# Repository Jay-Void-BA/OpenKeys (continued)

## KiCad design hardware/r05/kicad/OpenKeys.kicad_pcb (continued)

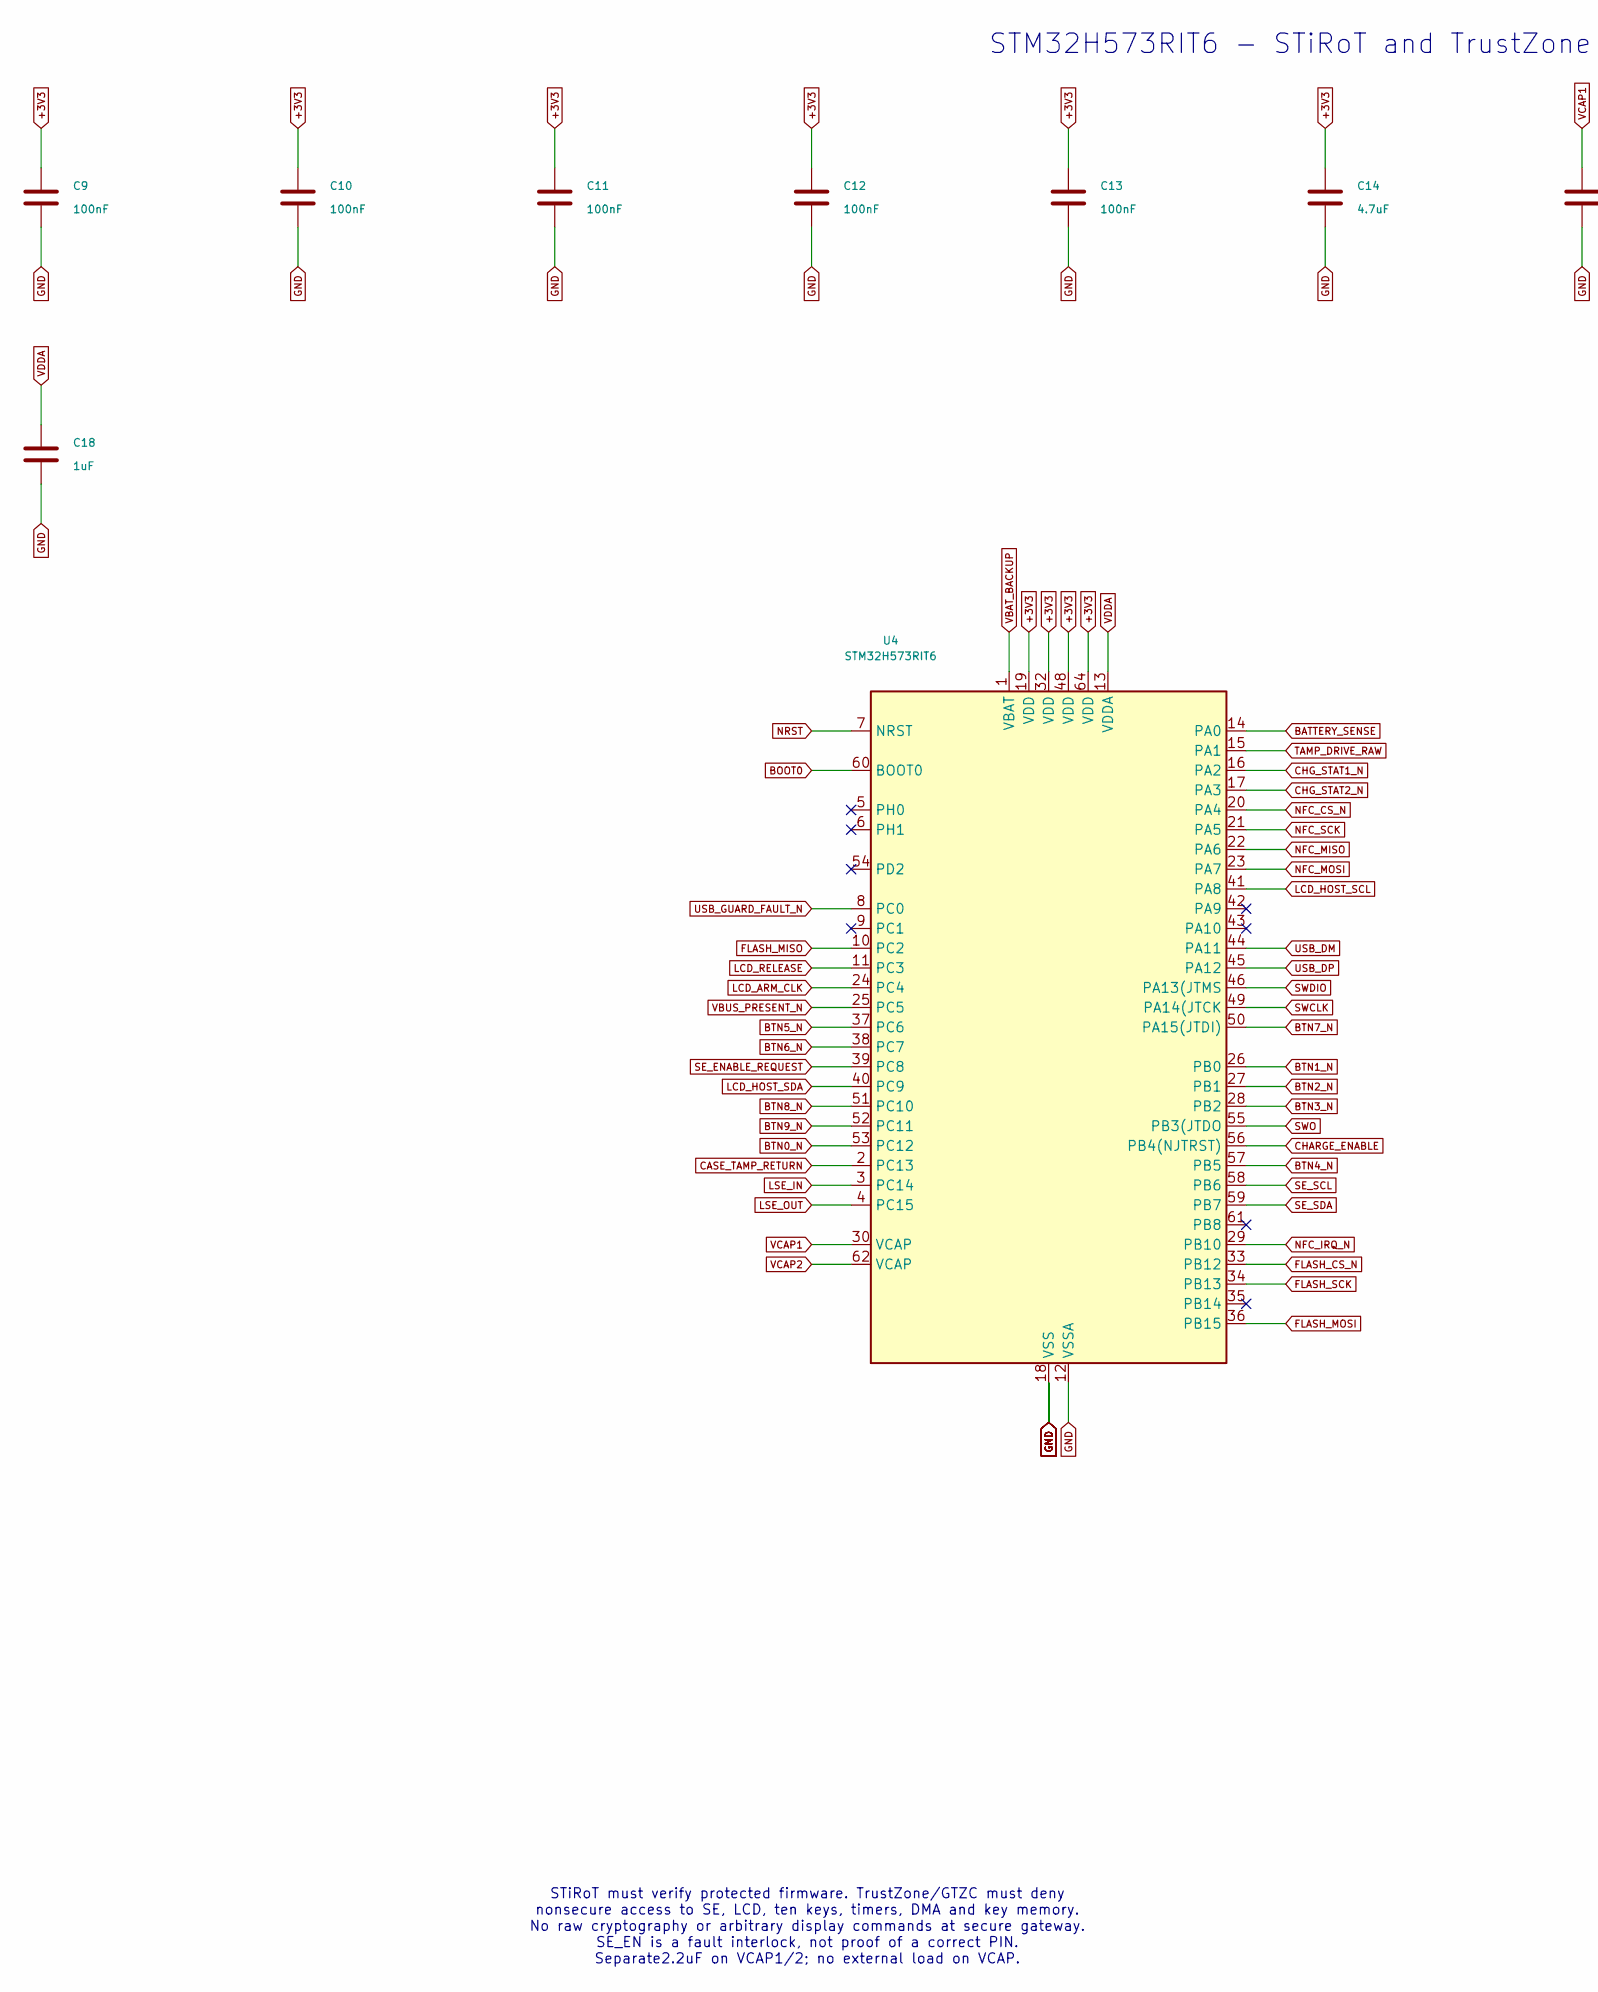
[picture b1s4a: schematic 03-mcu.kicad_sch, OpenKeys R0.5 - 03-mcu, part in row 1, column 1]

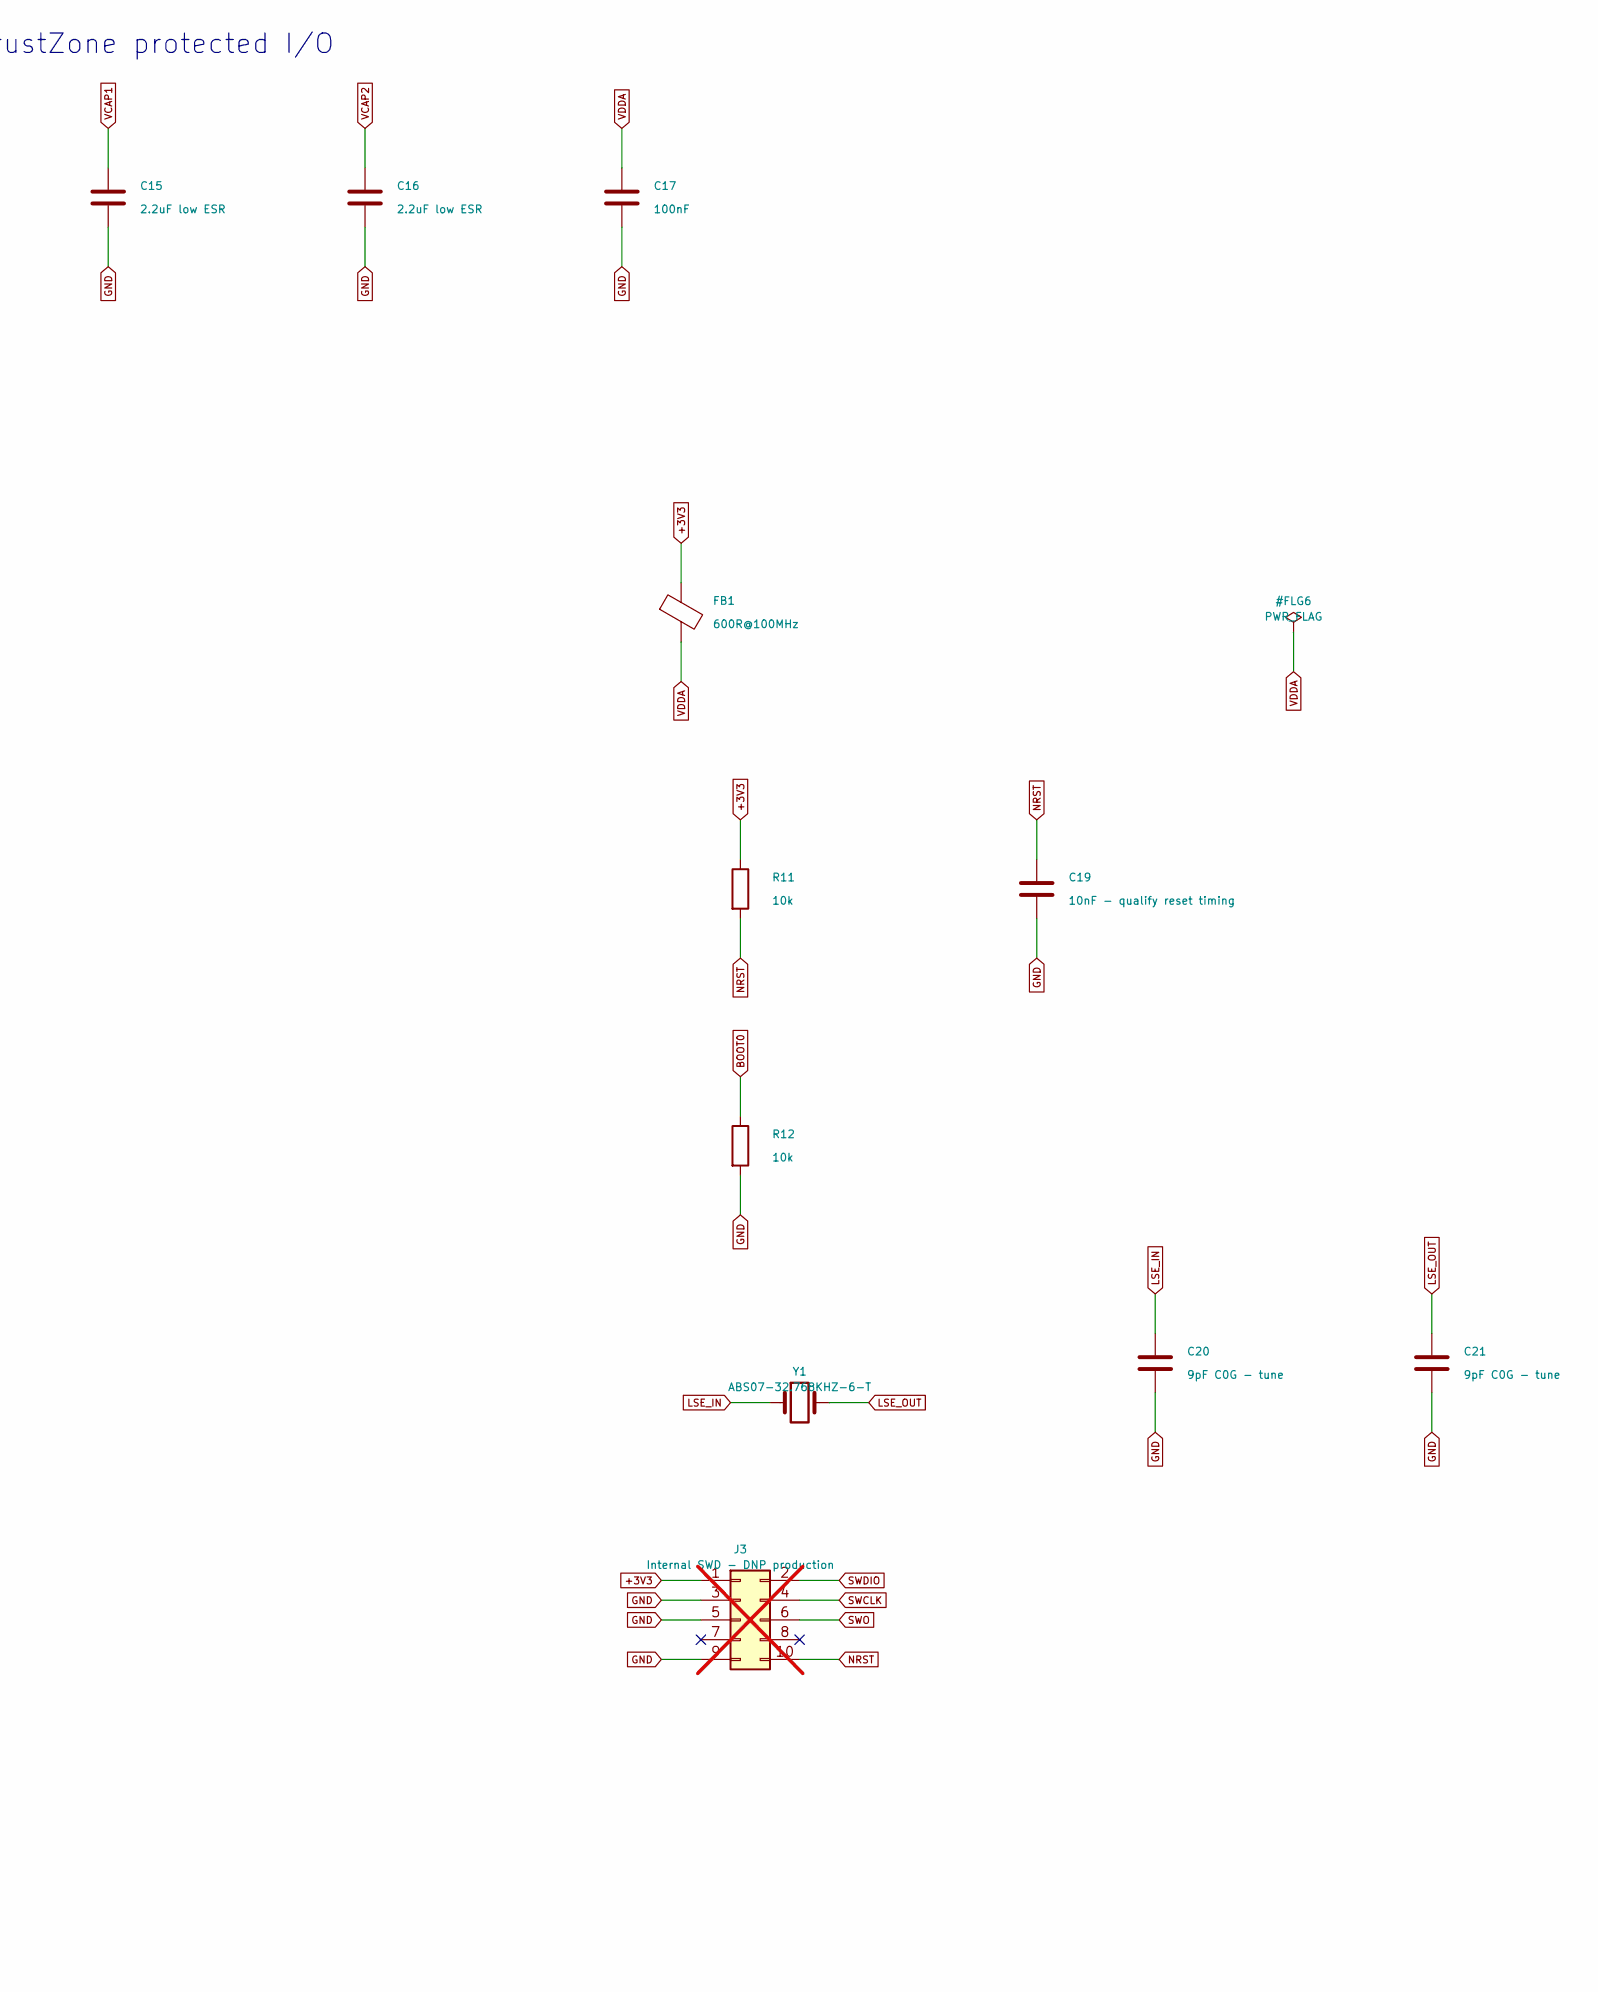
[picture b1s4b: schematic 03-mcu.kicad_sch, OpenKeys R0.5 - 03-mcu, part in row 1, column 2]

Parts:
C9, C10, C11, C12, C13, C17: 100nF; C_0603_1608Metric
C14: 4.7uF; C_0805_2012Metric
C15, C16: 2.2uF low ESR; C_0805_2012Metric
C18: 1uF; C_0805_2012Metric
C19: 10nF - qualify reset timing; C_0603_1608Metric
C20, C21: 9pF C0G - tune; C_0603_1608Metric
FB1: 600R@100MHz; L_0603_1608Metric
J3: Internal SWD - DNP production; PinHeader_2x05_P1.27mm_Vertical; not fitted
R11, R12: 10k; R_0603_1608Metric
U4: STM32H573RIT6; LQFP-64_10x10mm_P0.5mm
Y1: ABS07-32.768KHZ-6-T; Crystal_SMD_3215-2Pin_3.2x1.5mm

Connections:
+3V3: C9.1, C10.1, C11.1, C12.1, C13.1, C14.1, FB1.1, J3.1, R11.1, U4.19 (VDD), U4.32 (VDD), U4.48 (VDD), U4.64 (VDD); also elsewhere on the board
BATTERY_SENSE: U4.14 (PA0); also elsewhere on the board
BOOT0: R12.1, U4.60 (BOOT0)
BTN0_N: U4.53 (PC12); also elsewhere on the board
BTN1_N: U4.26 (PB0); also elsewhere on the board
BTN2_N: U4.27 (PB1); also elsewhere on the board
BTN3_N: U4.28 (PB2); also elsewhere on the board
BTN4_N: U4.57 (PB5); also elsewhere on the board
BTN5_N: U4.37 (PC6); also elsewhere on the board
BTN6_N: U4.38 (PC7); also elsewhere on the board
BTN7_N: U4.50 (PA15(JTDI)); also elsewhere on the board
BTN8_N: U4.51 (PC10); also elsewhere on the board
BTN9_N: U4.52 (PC11); also elsewhere on the board
CASE_TAMP_RETURN: U4.2 (PC13); also elsewhere on the board
CHARGE_ENABLE: U4.56 (PB4(NJTRST)); also elsewhere on the board
CHG_STAT1_N: U4.16 (PA2); also elsewhere on the board
CHG_STAT2_N: U4.17 (PA3); also elsewhere on the board
FLASH_CS_N: U4.33 (PB12); also elsewhere on the board
FLASH_MISO: U4.10 (PC2); also elsewhere on the board
FLASH_MOSI: U4.36 (PB15); also elsewhere on the board
FLASH_SCK: U4.34 (PB13); also elsewhere on the board
GND: C9.2, C10.2, C11.2, C12.2, C13.2, C14.2, C15.2, C16.2, C17.2, C18.2, C19.2, C20.2, C21.2, J3.3, J3.5, J3.9, R12.2, U4.12 (VSSA), U4.18 (VSS), U4.31 (VSS), U4.47 (VSS), U4.63 (VSS); also elsewhere on the board
LCD_ARM_CLK: U4.24 (PC4); also elsewhere on the board
LCD_HOST_SCL: U4.41 (PA8); also elsewhere on the board
LCD_HOST_SDA: U4.40 (PC9); also elsewhere on the board
LCD_RELEASE: U4.11 (PC3); also elsewhere on the board
LSE_IN: C20.1, U4.3 (PC14), Y1.1
LSE_OUT: C21.1, U4.4 (PC15), Y1.2
NFC_CS_N: U4.20 (PA4); also elsewhere on the board
NFC_IRQ_N: U4.29 (PB10); also elsewhere on the board
NFC_MISO: U4.22 (PA6); also elsewhere on the board
NFC_MOSI: U4.23 (PA7); also elsewhere on the board
NFC_SCK: U4.21 (PA5); also elsewhere on the board
NRST: C19.1, J3.10, R11.2, U4.7 (NRST); also elsewhere on the board
SE_ENABLE_REQUEST: U4.39 (PC8); also elsewhere on the board
SE_SCL: U4.58 (PB6); also elsewhere on the board
SE_SDA: U4.59 (PB7); also elsewhere on the board
SWCLK: J3.4, U4.49 (PA14(JTCK)
SWDIO: J3.2, U4.46 (PA13(JTMS)
SWO: J3.6, U4.55 (PB3(JTDO)
TAMP_DRIVE_RAW: U4.15 (PA1); also elsewhere on the board
USB_DM: U4.44 (PA11); also elsewhere on the board
USB_DP: U4.45 (PA12); also elsewhere on the board
USB_GUARD_FAULT_N: U4.8 (PC0); also elsewhere on the board
VBAT_BACKUP: U4.1 (VBAT); also elsewhere on the board
VBUS_PRESENT_N: U4.25 (PC5); also elsewhere on the board
VCAP1: C15.1, U4.30 (VCAP)
VCAP2: C16.1, U4.62 (VCAP)
VDDA: C17.1, C18.1, FB1.2, U4.13 (VDDA)

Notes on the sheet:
STM32H573RIT6 - STiRoT and TrustZone protected I/O
STiRoT must verify protected firmware. TrustZone/GTZC must deny nonsecure access to SE, LCD, ten keys, timers, DMA and key memory. No raw cryptography or arbitrary display commands at secure gateway. SE_EN is a fault interlock, not proof of a correct PIN. Separate2.2uF on VCAP1/2; no external load 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

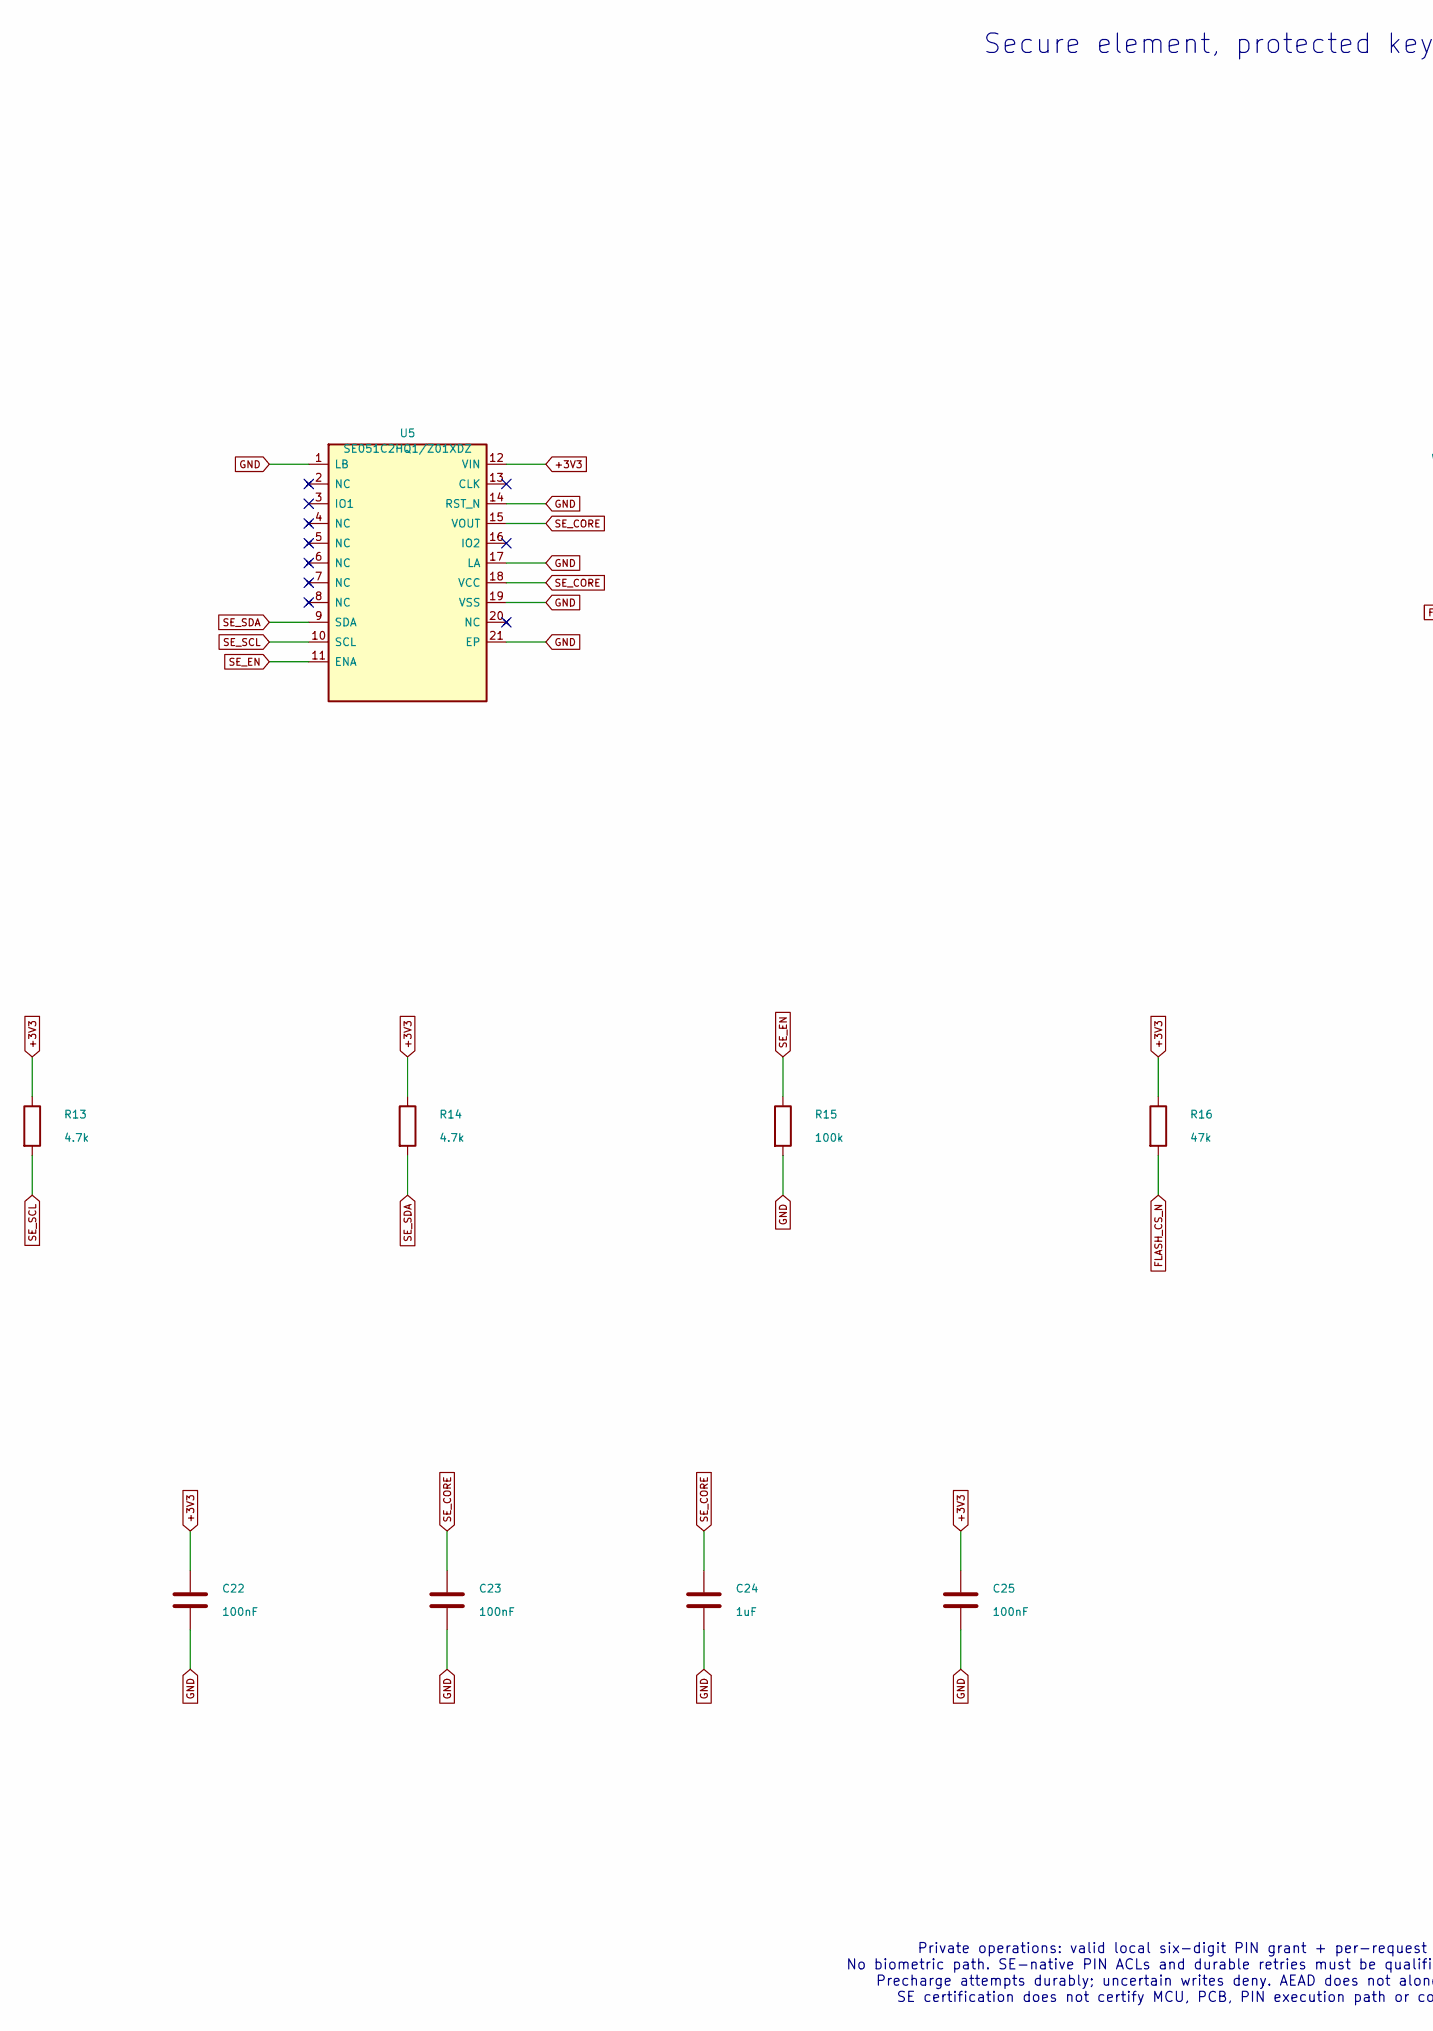
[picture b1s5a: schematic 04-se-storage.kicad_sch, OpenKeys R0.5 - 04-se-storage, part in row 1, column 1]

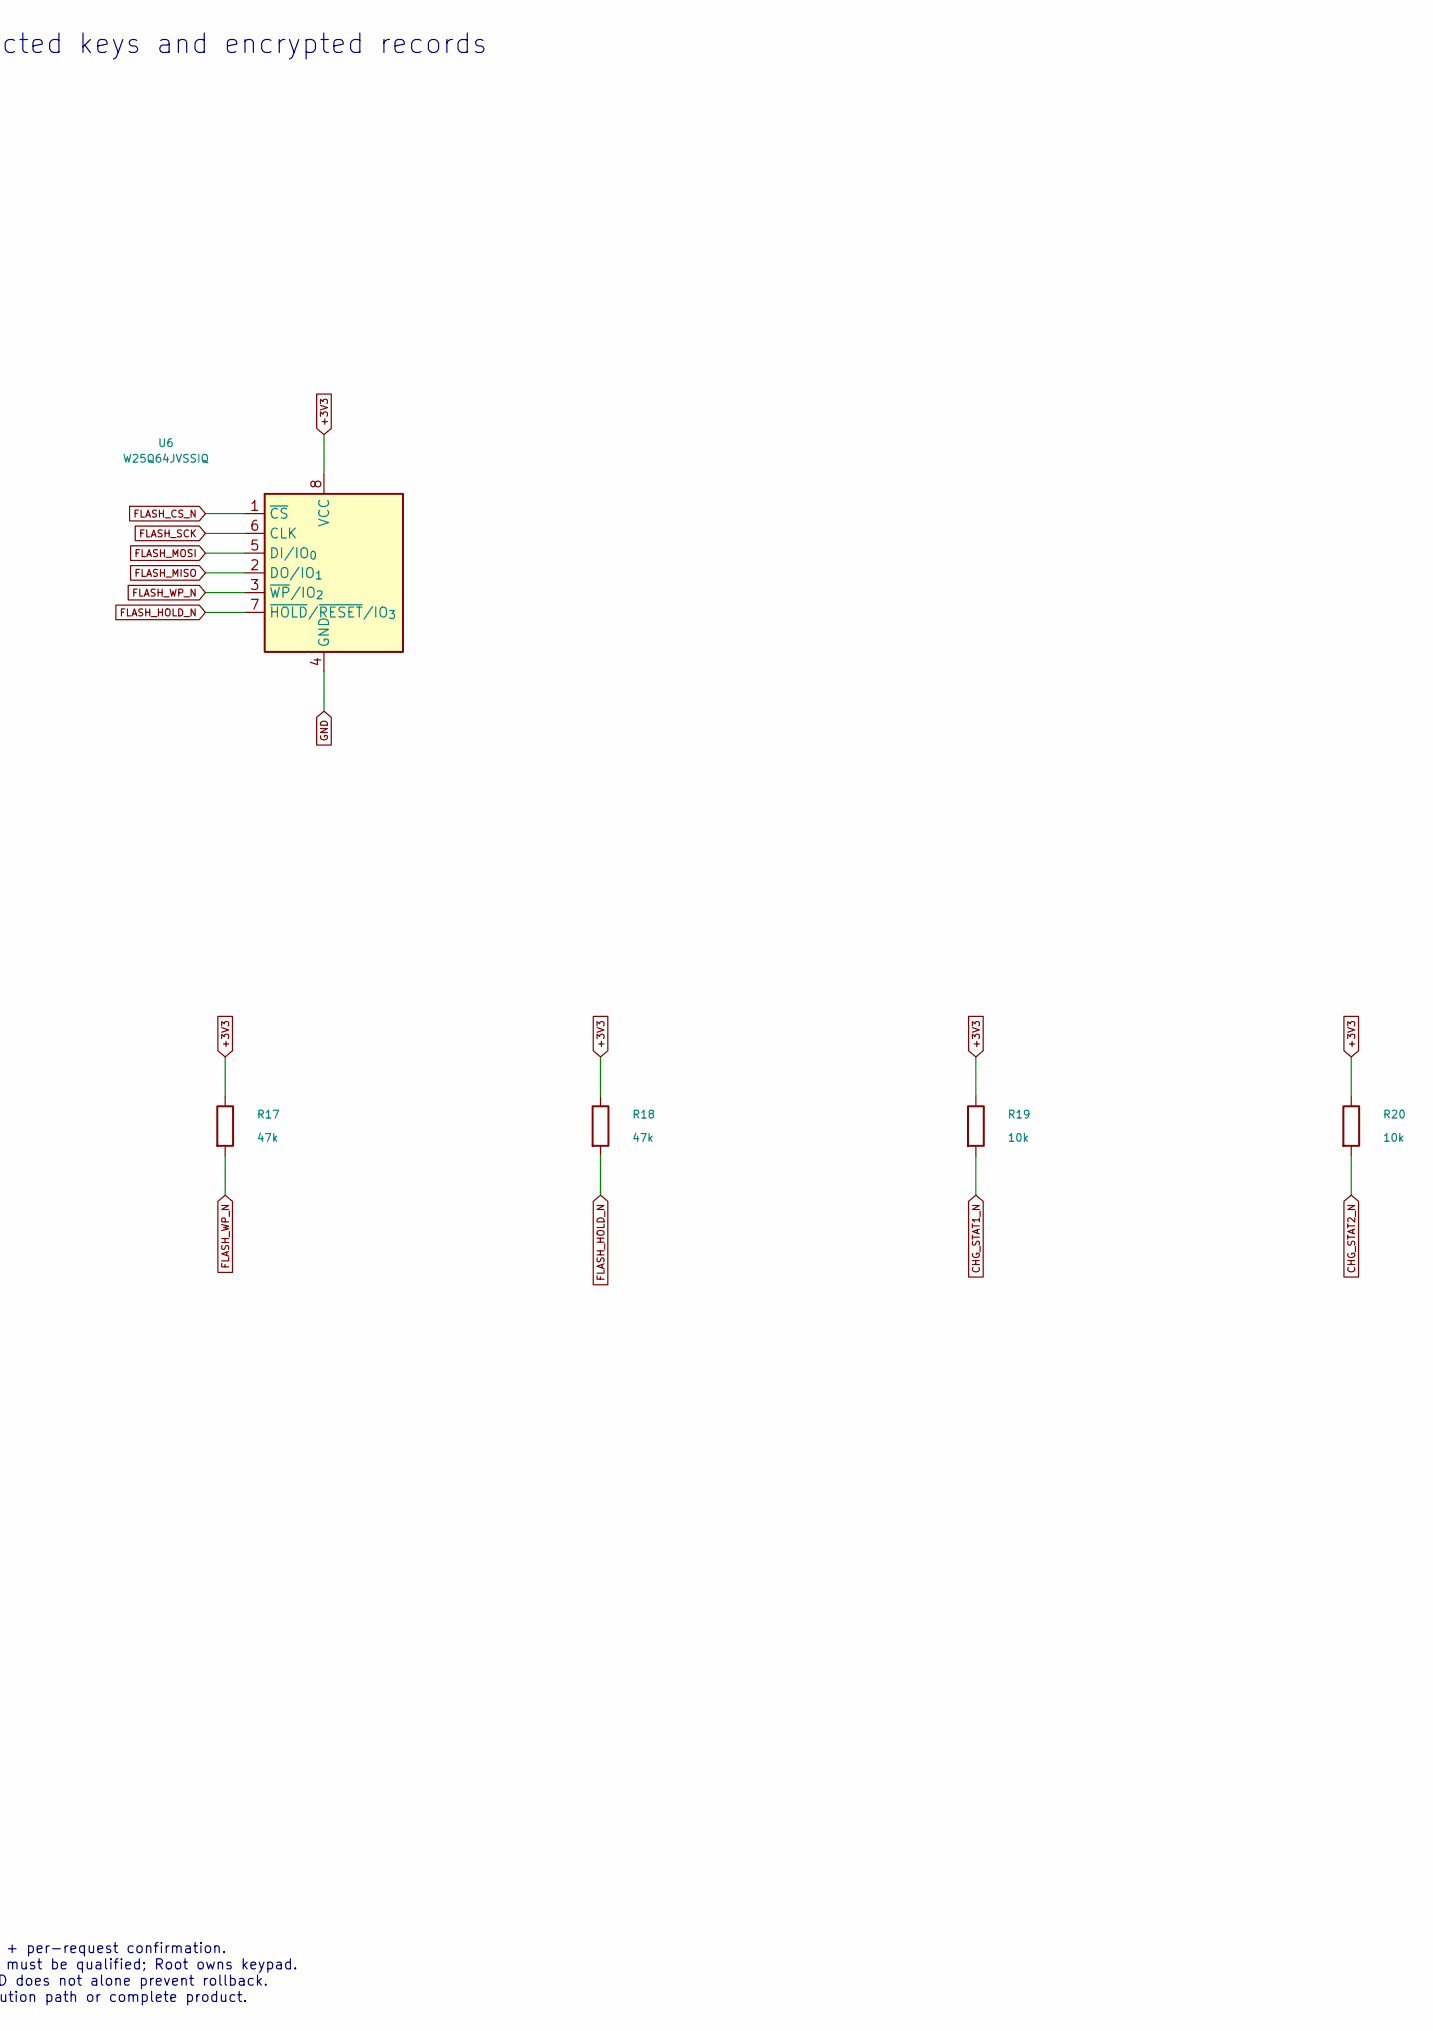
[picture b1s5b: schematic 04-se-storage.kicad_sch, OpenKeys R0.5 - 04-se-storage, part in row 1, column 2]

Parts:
C22, C23, C25: 100nF; C_0603_1608Metric
C24: 1uF; C_0805_2012Metric
R13, R14: 4.7k; R_0603_1608Metric
R15: 100k; R_0603_1608Metric
R16, R17, R18: 47k; R_0603_1608Metric
R19, R20: 10k; R_0603_1608Metric
U5: SE051C2HQ1/Z01XDZ; SE050_SOT1969-1_HX2QFN20
U6: W25Q64JVSSIQ; SOIC-8_5.3x5.3mm_P1.27mm

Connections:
+3V3: C22.1, C25.1, R13.1, R14.1, R16.1, R17.1, R18.1, R19.1, R20.1, U5.12 (VIN), U6.8 (VCC); also elsewhere on the board
CHG_STAT1_N: R19.2; also elsewhere on the board
CHG_STAT2_N: R20.2; also elsewhere on the board
FLASH_CS_N: R16.2, U6.1 (~CS); also elsewhere on the board
FLASH_HOLD_N: R18.2, U6.7 (~HOLD/~RESET/IO_{3})
FLASH_MISO: U6.2 (DO/IO_{1}); also elsewhere on the board
FLASH_MOSI: U6.5 (DI/IO_{0}); also elsewhere on the board
FLASH_SCK: U6.6 (CLK); also elsewhere on the board
FLASH_WP_N: R17.2, U6.3 (~WP/IO_{2})
GND: C22.2, C23.2, C24.2, C25.2, R15.2, U5.1 (LB), U5.14 (RST_N), U5.17 (LA), U5.19 (VSS), U5.21 (EP), U6.4 (GND); also elsewhere on the board
SE_CORE: C23.1, C24.1, U5.15 (VOUT), U5.18 (VCC)
SE_EN: R15.1, U5.11 (ENA); also elsewhere on the board
SE_SCL: R13.2, U5.10 (SCL); also elsewhere on the board
SE_SDA: R14.2, U5.9 (SDA); also elsewhere on the board

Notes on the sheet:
Secure element, protected keys and encrypted records
Private operations: valid local six-digit PIN grant + per-request confirmation. No biometric path. SE-native PIN ACLs and durable retries must be qualified; Root owns keypad. Precharge attempts durably; uncertain writes deny. AEAD does not alone prevent rollback. SE certification does not certify M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

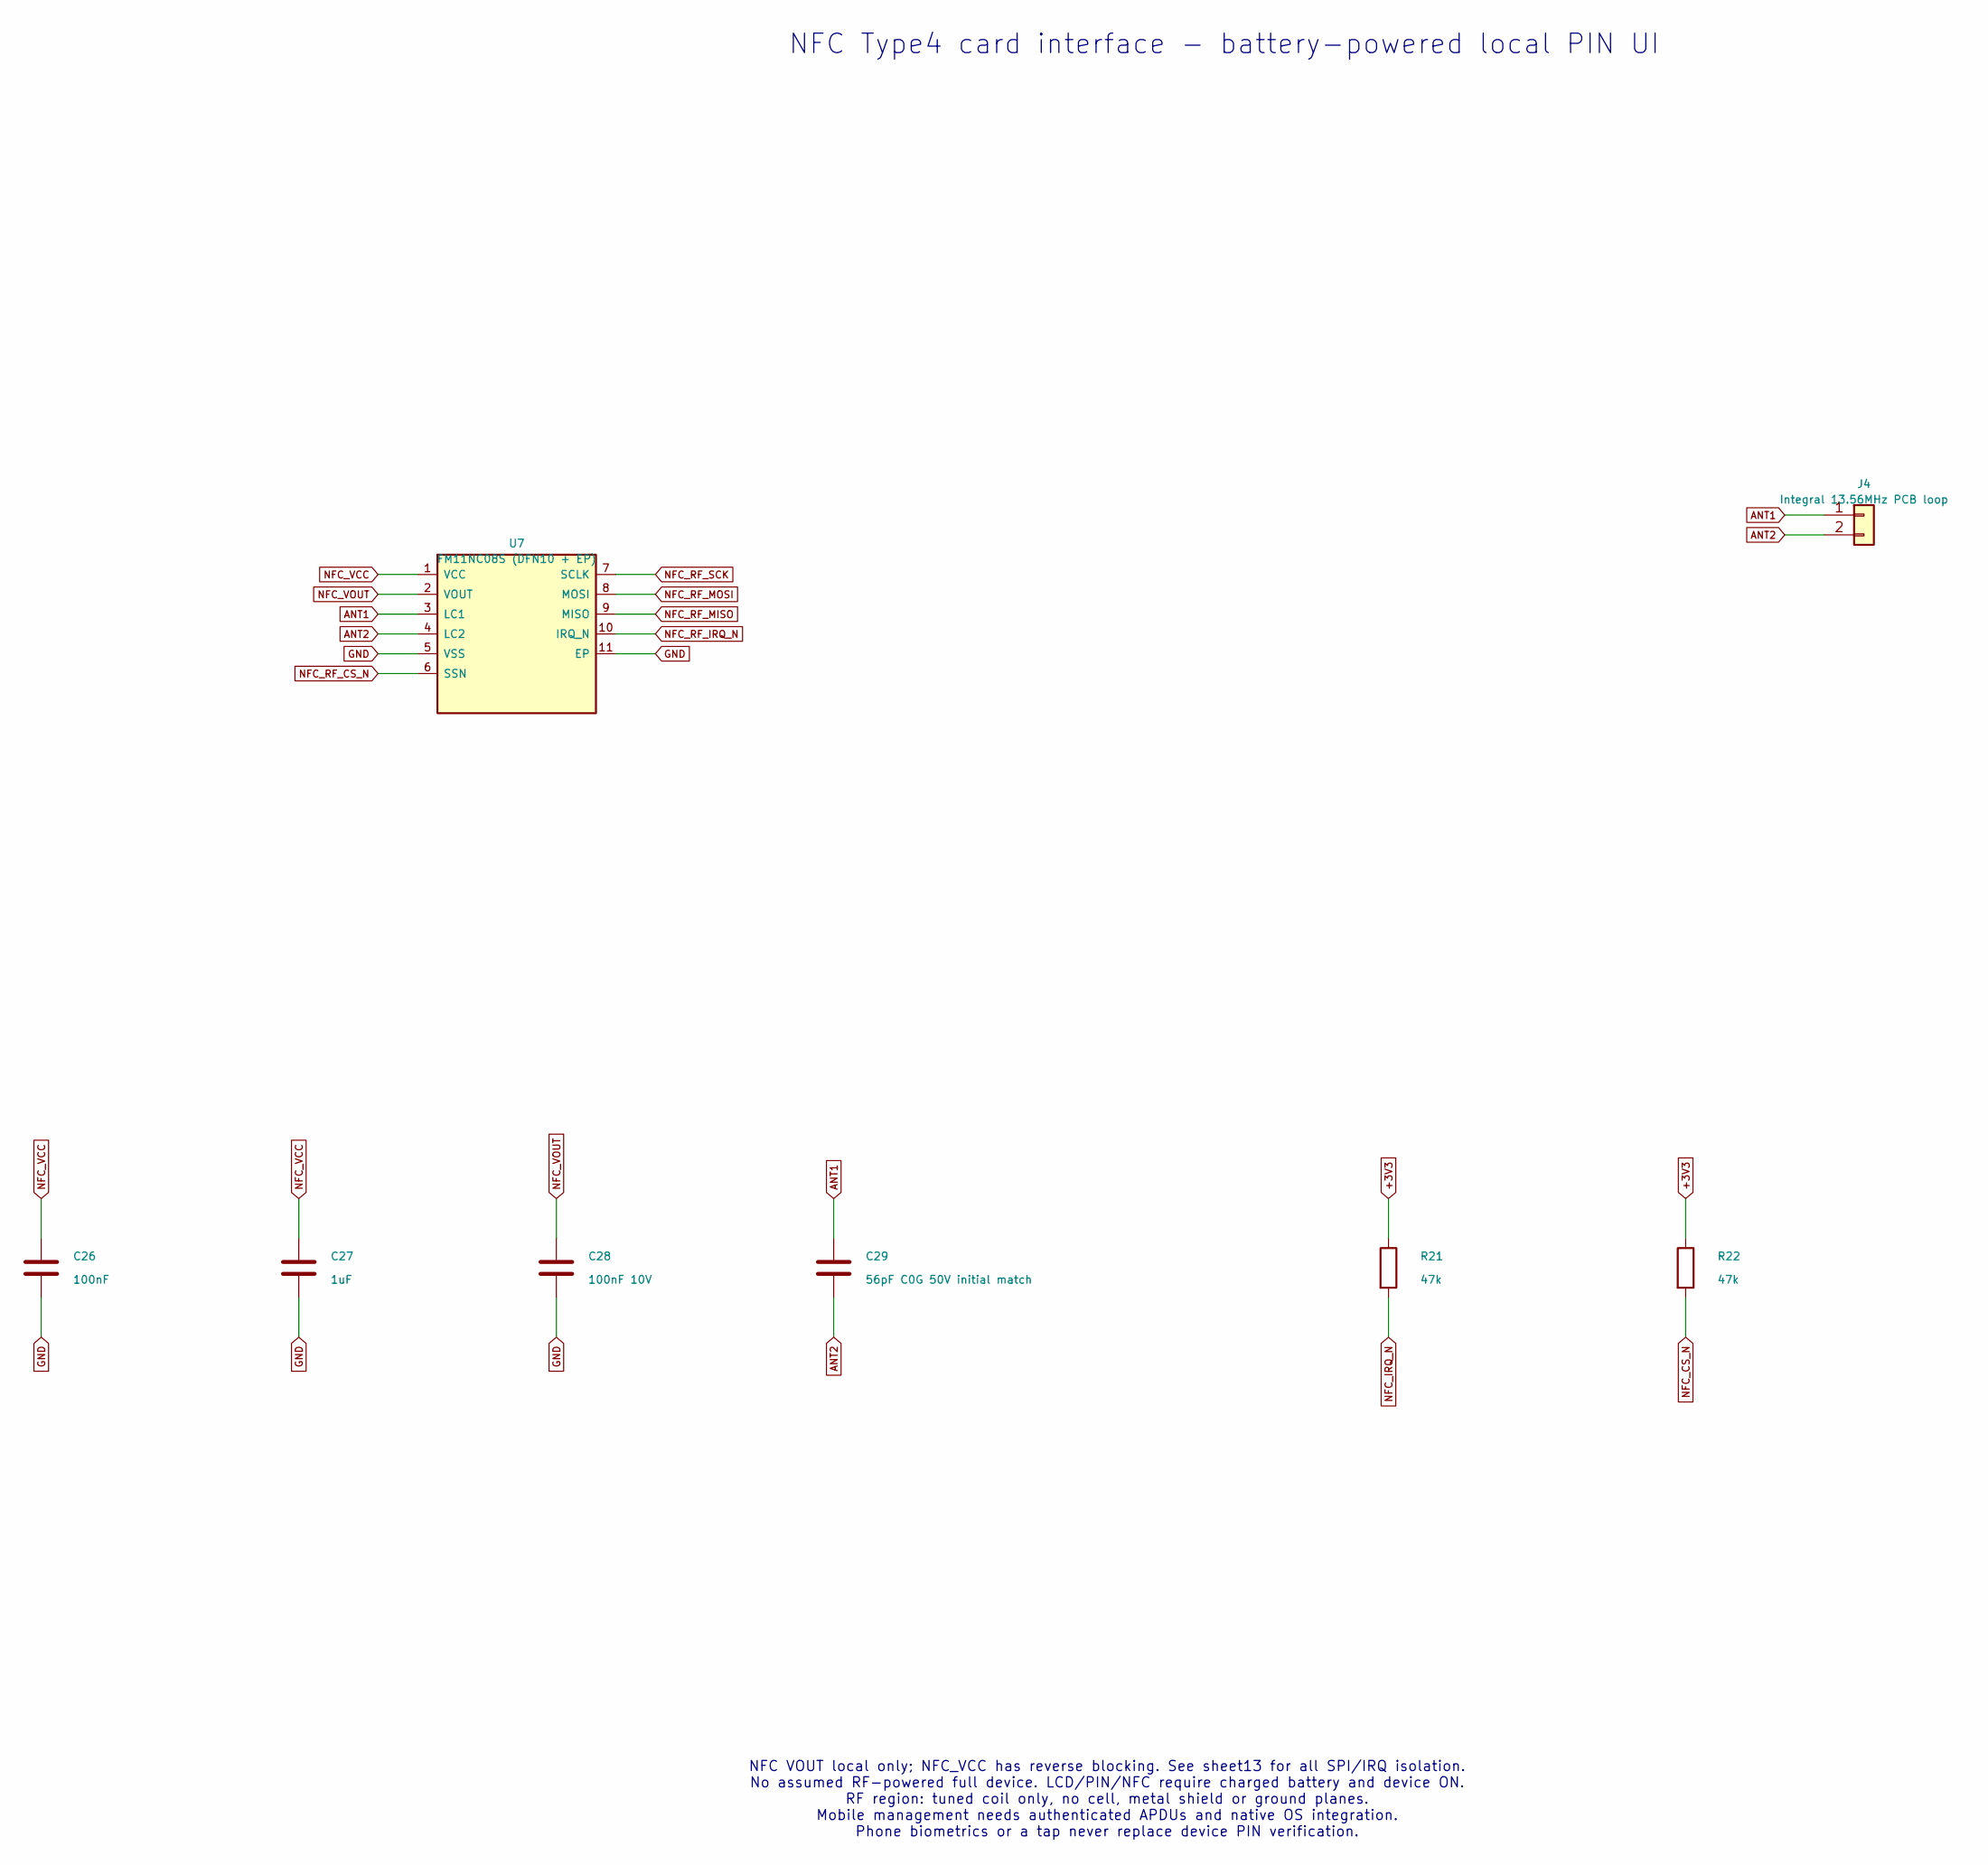
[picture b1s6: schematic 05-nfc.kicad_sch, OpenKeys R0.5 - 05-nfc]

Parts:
C26: 100nF; C_0603_1608Metric
C27: 1uF; C_0805_2012Metric
C28: 100nF 10V; C_0603_1608Metric
C29: 56pF C0G 50V initial match; C_0603_1608Metric
J4: Integral 13.56MHz PCB loop; NFC_PCB_Loop_4T_62x15
R21, R22: 47k; R_0603_1608Metric
U7: FM11NC08S (DFN10 + EP); FM11NC08S_DFN10_3x3_EP1.7x2.4

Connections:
+3V3: R21.1, R22.1; also elsewhere on the board
ANT1: C29.1, J4.1, U7.3 (LC1)
ANT2: C29.2, J4.2, U7.4 (LC2)
GND: C26.2, C27.2, C28.2, U7.5 (VSS), U7.11 (EP); also elsewhere on the board
NFC_CS_N: R22.2; also elsewhere on the board
NFC_IRQ_N: R21.2; also elsewhere on the board
NFC_RF_CS_N: U7.6 (SSN); also elsewhere on the board
NFC_RF_IRQ_N: U7.10 (IRQ_N); also elsewhere on the board
NFC_RF_MISO: U7.9 (MISO); also elsewhere on the board
NFC_RF_MOSI: U7.8 (MOSI); also elsewhere on the board
NFC_RF_SCK: U7.7 (SCLK); also elsewhere on the board
NFC_VCC: C26.1, C27.1, U7.1 (VCC); also elsewhere on the board
NFC_VOUT: C28.1, U7.2 (VOUT)

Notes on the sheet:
NFC Type4 card interface - battery-powered local PIN UI
NFC VOUT local only; NFC_VCC has reverse blocking. See sheet13 for all SPI/IRQ isolation. No assumed RF-powered full device. LCD/PIN/NFC require charged battery and device ON. RF region: tuned coil only, no cell, metal shield or ground planes. Mobile management needs authenticated APDUs and native 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
